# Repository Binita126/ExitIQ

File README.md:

# ExitIQ — Edge AI Dynamic Emergency Evacuation Guidance Terminal

**ExitIQ** is an ESP32-S3-powered, decentralized Edge AI emergency evacuation guidance terminal designed to replace obsolete static signage with real-time, dynamic egress routing during smoke and fire emergencies.

---

## 1. Project Purpose & Problem Statement

Conventional fire evacuation systems rely on static exit signs and centralized alarms. In modern multi-story and industrial facilities, static signage presents critical failure modes:
1. **Blind Routing:** Static signs guide occupants toward fixed exits regardless of whether the path is blocked by thermal barriers or smoke.
2. **Panic Bottlenecks:** Occupants blindly funnel into primary stairwells, exacerbating lethal crushing and congestion.
3. **Single Point of Failure:** Centralized building management systems (BMS) often fail when fire severs cabling or data uplinks.

**The ExitIQ Solution:**  
ExitIQ operates as an autonomous, localized terminal. By monitoring real-time environmental vectors (ambient temperature and combustion off-gassing) on-device, each terminal independently evaluates hazard threat levels and actuates directional strobe arrays and an acoustic alarm to steer occupants along the safest verified egress route.

---

## 2. Key Engineering Features

- **Edge Controller:** Espressif ESP32-S3 (Dual-Core Xtensa LX7 @ 240 MHz, 8 MB Octal Flash, 8 MB Octal PSRAM) running localized inference and egress routing.
- **Environmental Sensing Bay:**
  - **Sensirion SHT40-AD1B:** High-accuracy ambient temperature ($\pm 0.2^\circ\text{C}$) and relative humidity monitoring.
  - **Sensirion SGP40-DIS-R4:** Metal-oxide (MOx) VOC Air Quality Index sensor detecting pyrolysis and volatile combustion by-products.
  - *Thermal Isolation:* FR4 slot cutout isolating the sensor bay from MCU heat dissipation.
- **Active Evacuation Signaling:**
  - **Directional Array:** 8× Worldsemi WS2812B addressable 5050 RGB LEDs with active logic-level conversion (TI SN74AHCT1G125).
  - **Status Interface:** 0.96" 128×64 OLED display (SSD1306 via I2C).
  - **Acoustic Warning:** CUI Devices CMT-8540S-SMT 85 dBA buzzer driven by an active 2N7002 N-channel MOSFET with 1N4148 flyback clamp.
- **Power Management & Fail-Safe Autonomy:**
  - **Dynamic Power-Path:** TI BQ24074 managing external 5V USB-C power and seamless battery handover without system brownout.
  - **Integrated Li-Ion Battery:** Single-cell 18650 / Li-Po cell with DW01A-G supervisor and FS8205A dual-FET protection.
  - **Synchronous Boost:** TI TPS61023 (90%+ efficiency) stepping battery voltage up to 5.0 V for the directional LED array.

---

## 3. System Architecture

```mermaid
flowchart TD
    subgraph Power ["Power Subsystem"]
        USB["USB-C 5V Input"] --> BQ["TI BQ24074 Power-Path & Charger"]
        BAT["3.7V Li-Ion Battery"] <--> PROT["DW01A + FS8205A Protection"]
        PROT <--> BQ
        BQ -->|VSYS| BOOST["TI TPS61023 5V Boost"]
        BQ -->|VSYS| LDO["3.3V LDO on DevKit"]
    end

    subgraph Controller ["Core Processing"]
        LDO --> ESP["ESP32-S3-DevKitC-1 (Xtensa LX7)"]
        ESP -->|ADC Divider| VBAT_MON["Battery Monitor"]
    end

    subgraph Sensors ["Isolated Environmental Bay"]
        ESP -->|I2C 3.3V| SHT["Sensirion SHT40 (Temp/RH)"]
        ESP -->|I2C 3.3V| SGP["Sensirion SGP40 (VOC AQI)"]
    end

    subgraph Indicators ["Dynamic Actuation"]
        ESP -->|GPIO| SHIFT["SN74AHCT1G125 Level Shifter"]
        BOOST -->|5.0V| WS["8x WS2812B Directional LEDs"]
        SHIFT -->|Data| WS
        ESP -->|GPIO PWM| BUZZ["2N7002 + 85dBA Buzzer"]
        ESP -->|I2C 3.3V| OLED["SSD1306 128x64 OLED"]
    end
```

---

## 4. Repository Structure

```
ExitIQ_GitHub_Release/
├── README.md                                  # Master project guide and verification summary
├── LICENSE                                    # MIT License
├── .gitignore                                 # KiCad, CAD, and OS exclusion rules
├── DESIGN_NOTES.md                            # Complete engineering architecture & power budget
├── hardware/
│   ├── schematics/
│   │   ├── ExitIQ.kicad_sch                   # Authoritative KiCad schematic
│   │   ├── ExitIQ.kicad_pro                   # KiCad project configuration
│   │   ├── ExitIQ.pdf                         # Full schematic release print
│   │   ├── ExitIQ.net                         # Netlist cross-probing file
│   │   └── fp-lib-table / sym-lib-table       # Relative library tables
│   ├── pcb/
│   │   ├── ExitIQ.kicad_pcb                   # Authoritative 100% routed 2-layer PCB
│   │   ├── ExitIQ.kicad_pro                   # PCB project settings
│   │   └── fp-lib-table                       # PCB footprint table
│   └── libraries/
│       ├── symbols/ExitIQ.kicad_sym           # Custom schematic symbols
│       └── footprints.pretty/                 # Custom footprints (e.g., SGP40 DFN-6)
├── mechanical/
│   ├── catia/
│   │   ├── ExitIQ_Enclosure_Assembly_ReleaseCandidate.CATProduct  # Authoritative RC assembly
│   │   ├── ExitIQ_Enclosure_Base.CATPart      # Base tub with 4 concentric standoffs
│   │   ├── ExitIQ_Enclosure_Lid_RC.CATPart    # Centered 55x8mm LED slot lid
│   │   ├── ExitIQ_PCB.CATPart                 # PCB substrate solid model
│   │   ├── [20 Component CATParts]            # Native solid bodies for all components
│   │   ├── build_catia_enclosure.vbs          # CATIA automation script
│   │   └── CATIA_ENCLOSURE_SPEC.md            # Mechanical specifications
│   ├── exports/
│   │   ├── ExitIQ_Enclosure_Assembly_ReleaseCandidate.step # Neutral 3D STEP assembly
│   │   ├── ExitIQ_Enclosure_Base.step         # Base STEP model
│   │   ├── ExitIQ_Enclosure_Lid_RC.step       # Lid STEP model
│   │   ├── ExitIQ.step                        # PCB 3D STEP model
│   │   └── ExitIQ_BoardOutline_Mounting.dxf   # 2D CAD profile with M3 hole centers
│   └── cad/
│       └── ExitIQ_BoardOutline_Mounting.dxf
├── fabrication/
│   ├── MANUFACTURING_SPEC.md                  # Complete PCB fabrication notes & stackup
│   ├── ExitIQ_Gerber_Drill_Package.zip        # Consolidated manufacturing ZIP
│   ├── assembly/
│   │   ├── ExitIQ_Assembly_BOM.csv            # Audited 41-line grouped BOM (70 total parts)
│   │   └── ExitIQ_all_pos.csv                 # Centroid pick-and-place positions
│   ├── drill/
│   │   ├── ExitIQ-PTH.drl / ExitIQ-NPTH.drl   # NC Excellon drill files
│   │   └── ExitIQ_drill_report.rpt            # Hole count and tooling breakdown
│   └── gerbers/                               # 9 RS-274X copper, mask, paste, silk & edge layers
├── presentation/
│   ├── ExitIQ_Stage2_Final_With_Vishwakarma_Logo.pptx # Authoritative 20-slide presentation
│   └── PPT-ExitIQ_System_Architecture_Updated.pptx    # Baseline competition deck
├── reports/
│   ├── FINAL_SUBMISSION_STATUS.md             # Master deliverables readiness audit
│   ├── FINAL_VALIDATION_REPORT.md             # Consolidated verification report
│   ├── ExitIQ_CATIA_Final_Verification.md     # Mechanical fit and clearance audit
│   ├── Final_Engineering_Review.md            # Peer engineering review
│   ├── erc/ExitIQ_ERC_FinalReview.rpt         # KiCad ERC report (0 errors, 0 warnings)
│   └── drc/ExitIQ_DRC_FinalReview.rpt         # KiCad DRC report (0 unconnected, 0 shorts)
└── images/
    ├── mechanical/                            # High-resolution CATIA renders (Assembly, Lid, Base)
    ├── pcb/                                   # KiCad 3D renders and 2D layout drawings
    └── evidence/                              # Genuine CATIA & KiCad feature tree evidence
```

---

## 5. Instructions for Opening & Inspecting the Project

### Mechanical CAD (MCAD)
- **Primary Tool:** Dassault Systèmes CATIA V5-6R2022 (or compatible release).
- **Opening the Assembly:**
  1. Launch CATIA and open [`mechanical/enclosure/ExitIQ_Enclosure_Assembly_ReleaseCandidate.CATProduct`](mechanical/enclosure/ExitIQ_Enclosure_Assembly_ReleaseCandidate.CATProduct).
  2. All part links resolve locally within the directory.
- **Universal 3D CAD (FreeCAD, Fusion 360, SolidWorks, STEP Viewer):**
  - Open the neutral ISO 10303 STEP file: [`mechanical/exports/ExitIQ_Enclosure_Assembly_ReleaseCandidate.step`](mechanical/exports/ExitIQ_Enclosure_Assembly_ReleaseCandidate.step).
  - Open the PCB 3D STEP file: [`mechanical/exports/ExitIQ.step`](mechanical/exports/ExitIQ.step).

### Electrical CAD (ECAD)
- **Primary Tool:** KiCad 10.0.6 (or KiCad 8/9+ with symbol migration).
- **Opening Schematic:**
  1. Open [`hardware/schematics/ExitIQ.kicad_pro`](hardware/schematics/ExitIQ.kicad_pro) or [`hardware/schematics/ExitIQ.kicad_sch`](hardware/schematics/ExitIQ.kicad_sch).
  2. Symbols load automatically via [`hardware/schematics/sym-lib-table`](hardware/schematics/sym-lib-table).
- **Opening PCB Layout:**
  1. Open [`hardware/pcb/ExitIQ.kicad_pro`](hardware/pcb/ExitIQ.kicad_pro) or [`hardware/pcb/ExitIQ.kicad_pcb`](hardware/pcb/ExitIQ.kicad_pcb).
  2. Custom footprints load via [`hardware/pcb/fp-lib-table`](hardware/pcb/fp-lib-table).

### Manufacturing Deliverables
- Inspect Gerbers in KiCad GerbView or online viewers (e.g., JLCPCB/PCBWay viewer) using [`fabrication/ExitIQ_Gerber_Drill_Package.zip`](fabrication/ExitIQ_Gerber_Drill_Package.zip).
- SMT assembly BOM: [`fabrication/assembly/ExitIQ_Assembly_BOM.csv`](fabrication/assembly/ExitIQ_Assembly_BOM.csv) (41 unique items, 70 components total).

---

## 6. Implementation Status & Verification Transparency

| Subsystem / Metric | Status | Evidence / Log File |
| :--- | :--- | :--- |
| **Schematic ERC** | `PASSED` (0 Errors, 0 Warnings) | [`reports/erc/ExitIQ_ERC_FinalReview.rpt`](reports/erc/ExitIQ_ERC_FinalReview.rpt) |
| **PCB Layout DRC** | `PASSED` (100% Routed, 0 Shorts) | [`reports/drc/ExitIQ_DRC_FinalReview.rpt`](reports/drc/ExitIQ_DRC_FinalReview.rpt) |
| **Unconnected Nets** | `0` (All 70 nets, 642 tracks connected) | [`reports/drc/ExitIQ_DRC_FinalReview.rpt`](reports/drc/ExitIQ_DRC_FinalReview.rpt) |
| **Ground Plane** | Continuous low-impedance B.Cu pour | [`fabrication/gerbers/ExitIQ-B_Cu.gbl`](fabrication/gerbers/ExitIQ-B_Cu.gbl) |
| **Mechanical Clearance** | 0 collisions, +2.40 mm top headroom | [`reports/ExitIQ_CATIA_Final_Verification.md`](reports/ExitIQ_CATIA_Final_Verification.md) |
| **LED Optical Window** | Centered $55 \times 8\text{ mm}$ slot over 8 LEDs | [`images/mechanical/ExitIQ_LED_RC_Alignment_Check.png`](images/mechanical/ExitIQ_LED_RC_Alignment_Check.png) |
| **Stage 2 Presentation** | 20 Slides complete with Vishwakarma Logo | [`presentation/ExitIQ_Stage2_Final_With_Vishwakarma_Logo.pptx`](presentation/ExitIQ_Stage2_Final_With_Vishwakarma_Logo.pptx) |

### Documented DFM CAM Waivers
In the spirit of complete engineering honesty:
1. **TPS61023 (U3) Fine-Pitch SOT-563 Pad Clearance ($0.150\text{ mm}$):** Standard package pin pitch ($0.50\text{ mm}$) requires standard fine-pitch CAM rule ($0.100\text{ mm}$ solder mask dam / gang mask).
2. **USB-C (J1) Unplated Alignment Peg Clearance ($0.1944\text{ mm}$):** Plastic mechanical locating posts have zero electrical connectivity and zero shorting risk.
3. **Sensor Demarcation:** The Sensirion SGP40 is a MOx-based VOC Air Quality Index sensor utilized for early pyrolysis gas detection. It is not an optical smoke detector certified under EN 54 or UL 268. Physical fire chamber calibration is scheduled for Stage 3 prototyping.

---

## 7. Competition & Team Credits

- **Competition:** Vishwakarma Awards 2026 (Maker Bhavan Foundation — MBF), Stage 2
- **Theme:** AI in Hardware & Manufacturing | Worker Safety & Hazard Prevention
- **Deliverables:** Stage 2 CAD, ECAD, Manufacturing Package, and Presentation Release

---

## 8. License

This project is licensed under the [MIT License](LICENSE).

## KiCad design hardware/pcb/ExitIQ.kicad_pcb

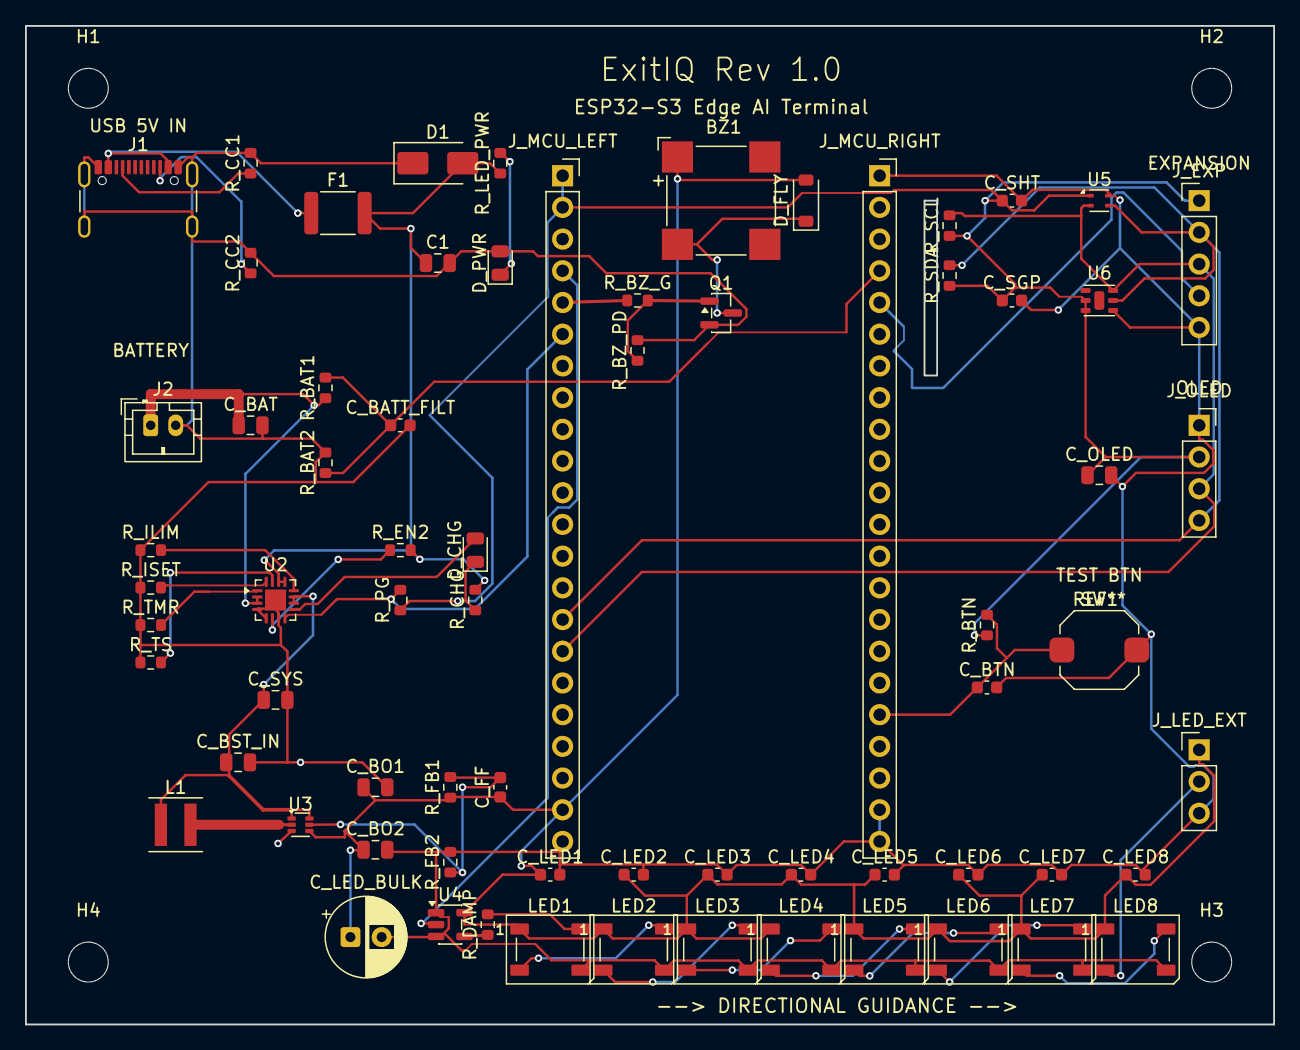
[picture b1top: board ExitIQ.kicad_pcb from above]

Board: 2 copper layers, 100.0 x 80.0 mm, 74 parts (0 on the bottom side), 39 nets.

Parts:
BZ1: CMT-8540S-SMT; MagneticBuzzer_CUI_CMT-8504-100-SMT
C1: 10uF 16V; C_0805_2012Metric
C_BAT: 10uF 16V; C_0805_2012Metric
C_BATT_FILT: 100nF; C_0603_1608Metric
C_BO1, C_BO2: 22uF 10V; C_0805_2012Metric
C_BST_IN: 10uF 16V; C_0805_2012Metric
C_BTN: 100nF; C_0603_1608Metric
C_FF: 22pF; C_0603_1608Metric
C_LED1, C_LED2, C_LED3, C_LED4, C_LED5, C_LED6, C_LED7, C_LED8: 100nF; C_0603_1608Metric
C_LED_BULK: 100uF 10V; CP_Radial_D6.3mm_P2.50mm
C_OLED: 10uF 16V; C_0805_2012Metric
C_SGP: 100nF; C_0603_1608Metric
C_SHT: 100nF; C_0603_1608Metric
C_SYS: 10uF 16V; C_0805_2012Metric
D1: SMAJ5.0A; D_SMA
D_CHG: ORANGE (CHG); LED_0805_2012Metric
D_FLY: 1N4148W; D_SOD-123
D_PWR: GREEN (MAINS); LED_0805_2012Metric
F1: 2.0A Hold; Fuse_1812_4532Metric
H1, H2, H3, H4: MountingHole_3.2mm_M3
J1: USB_C_5V_IN; USB_C_Receptacle_GCT_USB4105-xx-A_16P_TopMnt_Horizontal
J2: BATT_JST_PH; JST_PH_B2B-PH-K_1x02_P2.00mm_Vertical
J_EXP: SENSOR_EXP_5P; PinHeader_1x05_P2.54mm_Vertical
J_LED_EXT: EXT_LED_STRIP_3P; PinHeader_1x03_P2.54mm_Vertical
J_MCU_LEFT: DevKitC-1_J1; PinSocket_1x22_P2.54mm_Vertical
J_MCU_RIGHT: DevKitC-1_J3; PinSocket_1x22_P2.54mm_Vertical
J_OLED: OLED_SSD1306_4P; PinSocket_1x04_P2.54mm_Vertical
L1: 1.0uH 4.5A; L_Coilcraft_XxL4020
LED1, LED2, LED3, LED4, LED5, LED6, LED7, LED8: WS2812B; LED_WS2812B_PLCC4_5.0x5.0mm_P3.2mm
Q1: 2N7002; SOT-23
R_BAT1, R_BAT2: 100k 1%; R_0603_1608Metric
R_BTN: 10k; R_0603_1608Metric
R_BZ_G: 100; R_0603_1608Metric
R_BZ_PD: 100k; R_0603_1608Metric
R_CC1, R_CC2: 5.1k; R_0603_1608Metric
R_CHG: 1.5k; R_0603_1608Metric
R_DAMP: 330; R_0603_1608Metric
R_EN2: 10k; R_0603_1608Metric
R_FB1: 732k 1%; R_0603_1608Metric
R_FB2: 100k 1%; R_0603_1608Metric
R_ILIM: 1.18k 1%; R_0603_1608Metric
R_ISET: 1.0k 1%; R_0603_1608Metric
R_LED_PWR: 1.0k; R_0603_1608Metric
R_PG: 10k; R_0603_1608Metric
R_SCL: 4.7k 1%; R_0603_1608Metric
R_SDA: 4.7k 1%; R_0603_1608Metric
R_TMR: 47k; R_0603_1608Metric
R_TS: 10k 1%; R_0603_1608Metric
SW1: TEST_BTN; SW_Push_1TS009xxxx-xxxx-xxxx_6x6x5mm
U2: BQ24074RGTR; QFN-16-1EP_3x3mm_P0.5mm_EP1.7x1.7mm
U3: TPS61023DRLR; SOT-563
U4: 74AHCT1G125; SOT-23-5
U5: SHT40-AD1B; Sensirion_DFN-4_1.5x1.5mm_P0.8mm_SHT4x_NoCentralPad
U6: SGP40-DIS; Sensirion_DFN-6-1EP_2.44x2.44mm_P0.8mm

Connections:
+3V3: C_OLED.1, C_SGP.1, C_SHT.1, J_EXP.1, J_MCU_LEFT.1, J_MCU_LEFT.2, J_OLED.2, R_BTN.1, R_PG.1, R_SCL.1, R_SDA.1, U5.1, U6.1, U6.3
+5V: BZ1.1, C_BO1.1, C_BO2.1, C_FF.1, C_LED1.1, C_LED2.1, C_LED3.1, C_LED4.1, C_LED5.1, C_LED6.1, C_LED7.1, C_LED8.1, C_LED_BULK.1, D_FLY.2, J_LED_EXT.1, J_MCU_LEFT.21, LED1.1, LED2.1, LED3.1, LED4.1, LED5.1, LED6.1, LED7.1, LED8.1, R_FB1.1, U3.4, U4.5
/BATT_SENSE: C_BATT_FILT.1, J_MCU_RIGHT.4, R_BAT1.2, R_BAT2.1
/BUZZER_CTRL: J_MCU_LEFT.5, R_BZ_G.1
/CC1: J1.A5, R_CC1.1
/CC2: J1.B5, R_CC2.1
/EXP_ADC: J_EXP.4, J_MCU_RIGHT.5
/I2C_SCL: J_EXP.3, J_MCU_LEFT.16, J_OLED.3, R_SCL.2, U5.2, U6.5
/I2C_SDA: J_EXP.2, J_MCU_LEFT.15, J_OLED.4, R_SDA.2, U5.3, U6.4
/LED_CHAIN_IN: LED1.4, R_DAMP.2
/LED_DATA_3V3: J_MCU_LEFT.4, U4.2
/LED_EXT_DOUT: J_LED_EXT.2, LED8.2
/PGOOD: J_MCU_LEFT.6, R_PG.2, U2.8
/USER_BTN: C_BTN.1, J_MCU_RIGHT.18, R_BTN.2, SW1.1
/VBAT: C_BAT.1, J2.1, R_BAT1.1, U2.2, U2.3
/VBUS: F1.1, J1.A4, J1.A9, J1.B4, J1.B9
/VBUS_FUSED: C1.1, D1.2, F1.2, R_CHG.2, R_EN2.2, R_LED_PWR.1, U2.13, U2.14
/V_SYS: C_BST_IN.1, C_SYS.1, L1.1, U2.10, U2.11, U3.1, U3.6
GND: C1.2, C_BAT.2, C_BATT_FILT.2, C_BO1.2, C_BO2.2, C_BST_IN.2, C_BTN.2, C_LED1.2, C_LED2.2, C_LED3.2, C_LED4.2, C_LED5.2, C_LED6.2, C_LED7.2, C_LED8.2, C_LED_BULK.2, C_OLED.2, C_SGP.2, C_SHT.2, C_SYS.2, D1.1, D_PWR.2, J1.A1, J1.A12, J1.B1, J1.B12, J1.SH, J2.2, J_EXP.5, J_LED_EXT.3, J_MCU_LEFT.22, J_MCU_RIGHT.1, J_MCU_RIGHT.21, J_MCU_RIGHT.22, J_OLED.1, LED1.3, LED2.3, LED3.3, LED4.3, LED5.3, LED6.3, LED7.3, LED8.3, Q1.2, R_BAT2.2, R_BZ_PD.2, R_CC1.2, R_CC2.2, R_FB2.2, R_ILIM.1, R_ISET.1, R_TMR.1, R_TS.1, SW1.2, U2.4, U2.5, U2.7, U2.17, U3.3, U4.1, U4.3, U5.4, U6.2
unnamed: BZ1.2, D_FLY.1, Q1.3
unnamed: D_CHG.1, R_CHG.1
unnamed: D_CHG.2, U2.9
unnamed: D_PWR.1, R_LED_PWR.2
unnamed: LED1.2, LED2.4
unnamed: LED2.2, LED3.4
unnamed: LED3.2, LED4.4
unnamed: LED4.2, LED5.4
unnamed: LED5.2, LED6.4
unnamed: LED6.2, LED7.4
unnamed: LED7.2, LED8.4
unnamed: Q1.1, R_BZ_G.2, R_BZ_PD.1
unnamed: R_EN2.1, U2.6
unnamed: R_ILIM.2, U2.12
unnamed: R_ISET.2, U2.16
unnamed: R_TMR.2, U2.1
unnamed: R_TS.2, U2.15
unnamed: C_FF.2, R_FB1.2, R_FB2.1, U3.5
unnamed: L1.2, U3.2
unnamed: R_DAMP.1, U4.4
